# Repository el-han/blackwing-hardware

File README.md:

# Blackwing keyboard

The Blackwing keyboard is a vertically staggered split keyboard inspired by the [Mitosis keyboard](https://github.com/reversebias/mitosis).

## Features

- QMK firmware
- Cherry MX switches
- nRF52840 module
- NKRO as each switch is wired to its own GPIO
- Nordic's proprietary low power radio protocol
- Uses the receiver from the [Mitosis keyboard](https://github.com/reversebias/mitosis)
- Runs months to years on battery as it stays in deep sleep until a button is pressed or released
- PCB plate for plate mounted switches

## Todo

- Merge firmware into QMK project
- Use nRF 52840 dongle as receiver
- Build a ZMK based firmware
- Add Bluetooth support

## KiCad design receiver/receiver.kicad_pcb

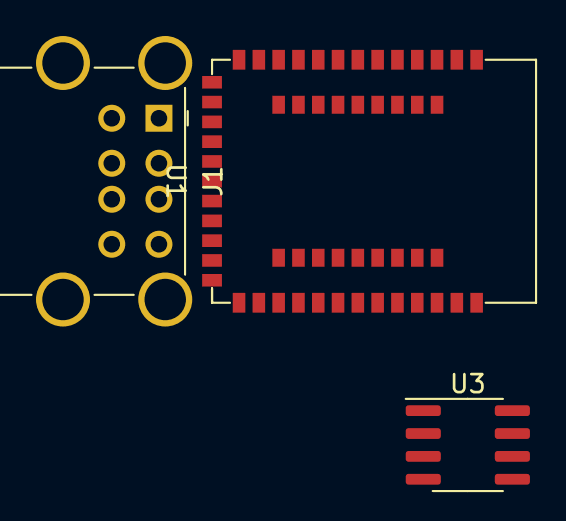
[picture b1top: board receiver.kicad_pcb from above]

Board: 2 copper layers, 4 parts (1 on the bottom side), 4 nets, no tracks yet.

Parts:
J1: USB_A; USB_A_Wuerth_61400826021_Horizontal_Stacked
U1: HOLYIOT-18010-NRF52840
U2: ATmega32U4-A; TQFP-44_10x10mm_P0.8mm
U3: AMS1117CS-3.3; SOIC-8_3.9x4.9mm_P1.27mm

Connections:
unnamed: U2.14 (VCC), U2.34 (VCC)
unnamed: U2.15 (GND), U2.23 (GND), U2.35 (GND), U2.43 (GND)
unnamed: U2.24 (AVCC), U2.44 (AVCC)
unnamed: U3.2 (VO), U3.3 (VO), U3.6 (VO), U3.7 (VO)

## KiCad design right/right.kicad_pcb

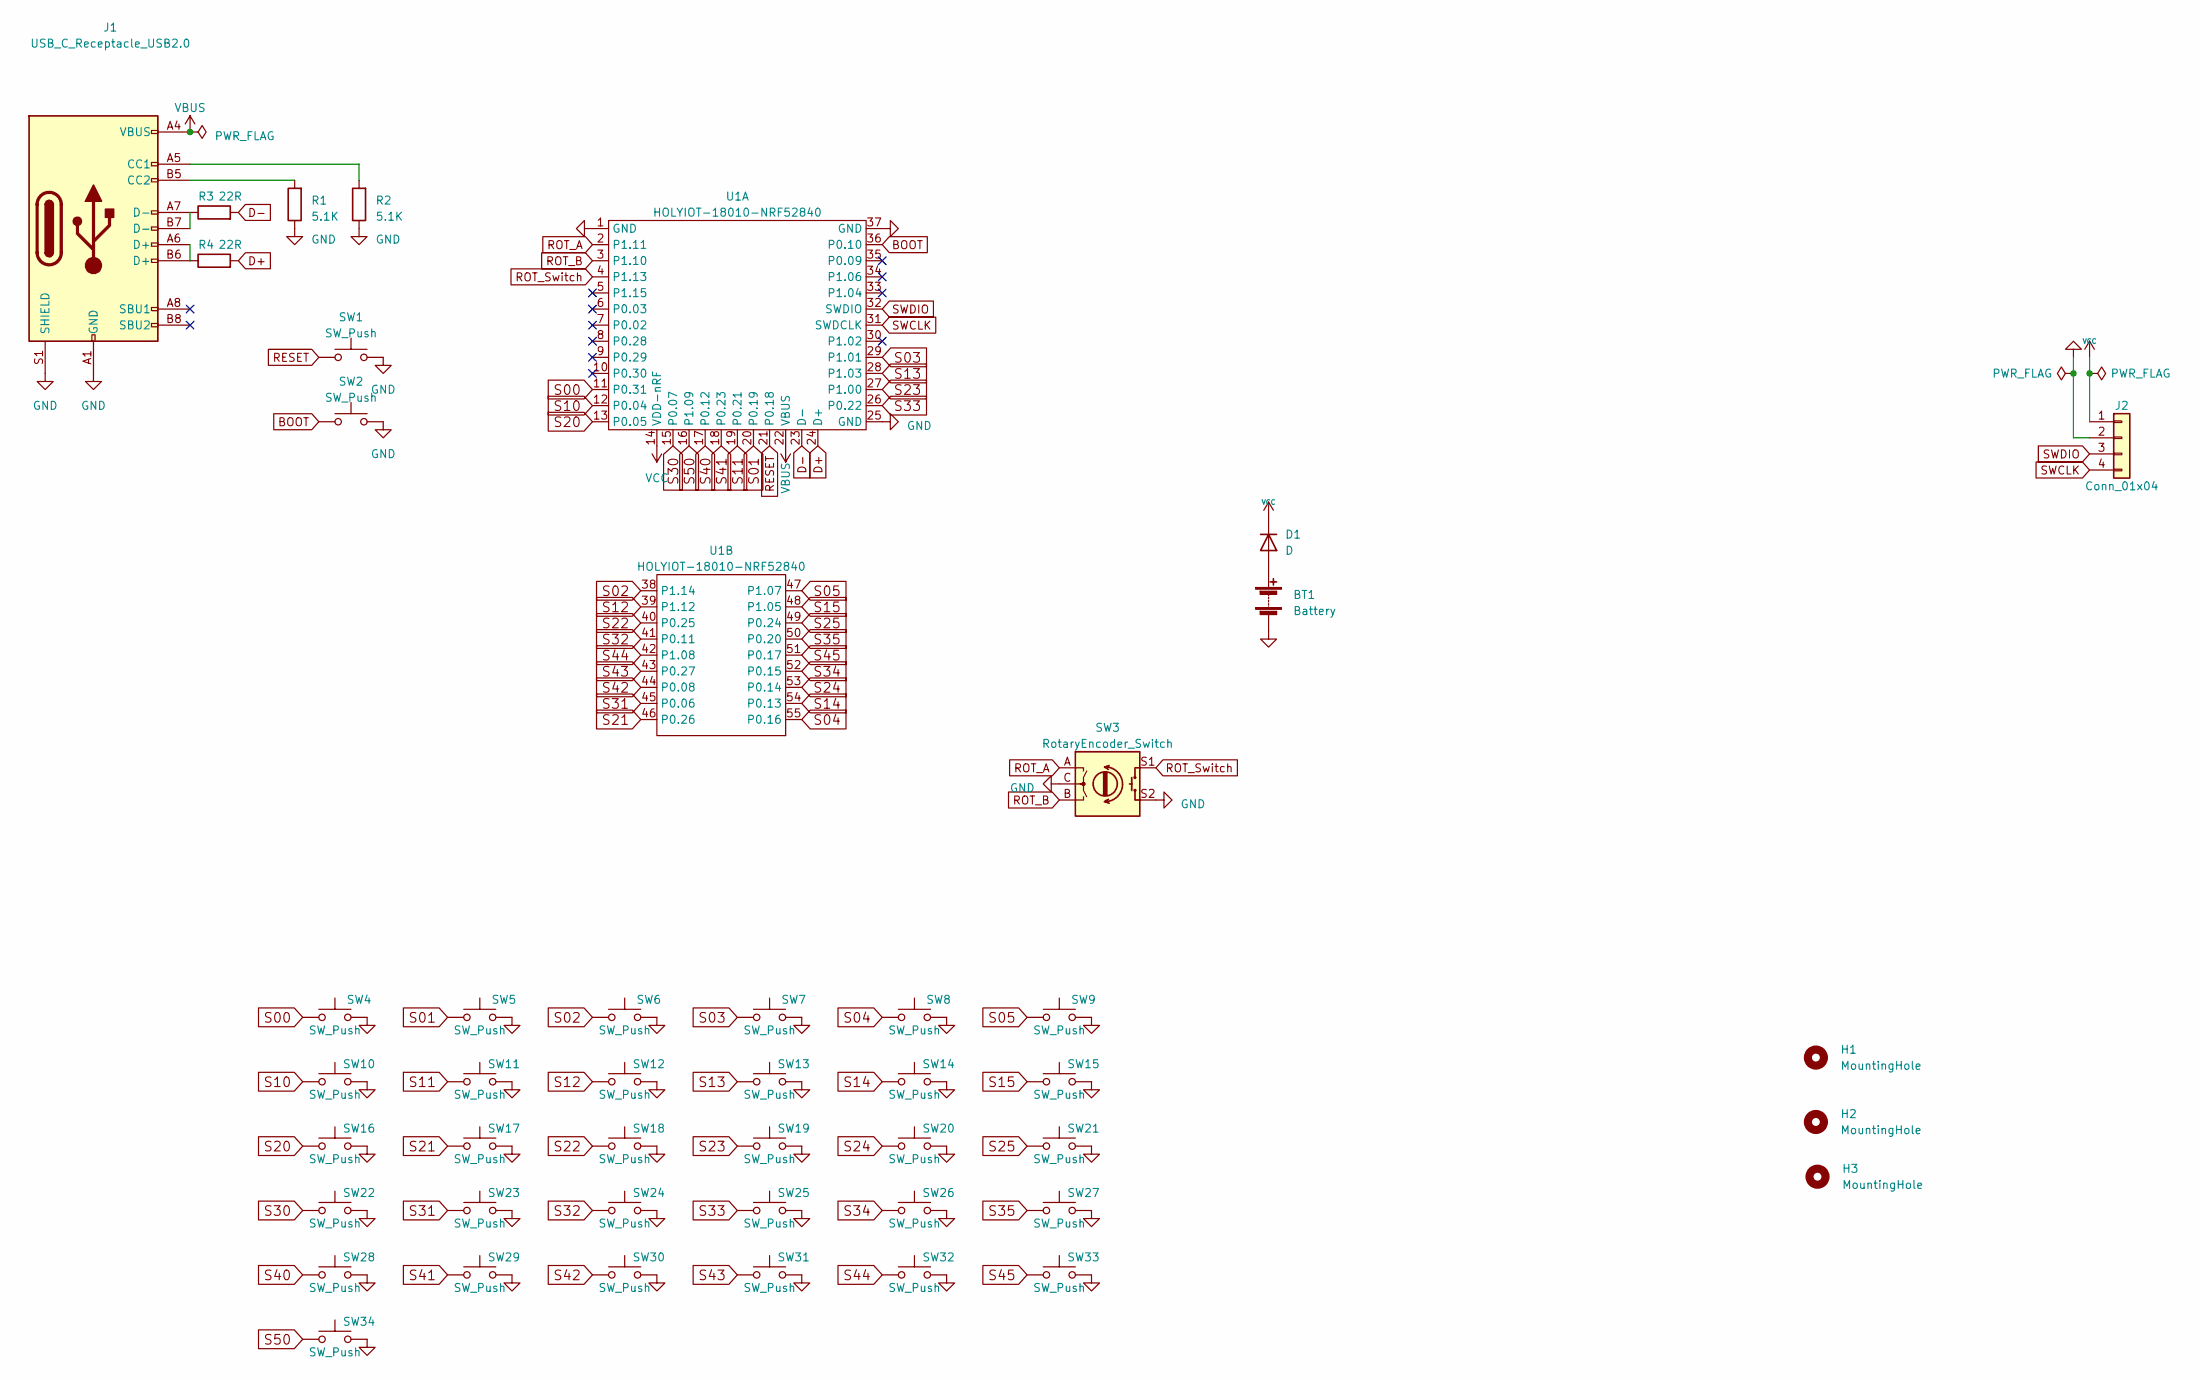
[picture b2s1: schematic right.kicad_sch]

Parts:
BT1: Battery; BatteryHolder_Keystone_2468_2xAAA
D1: D; D_SOD-123
H1, H2, H3: MountingHole; MountingHole_2.7mm_M2.5_DIN965
J1: USB_C_Receptacle_USB2.0; USB_C_Receptacle_GCT_USB4085
J2: Conn_01x04; Programming_Header
R1, R2: 5.1K; R_0603_1608Metric
R3, R4: 22R; R_0402_1005Metric
SW1, SW2: SW_Push; SW_Push_1P1T_NO_Vertical_Wuerth_434133025816
SW3: RotaryEncoder_Switch; RotaryEncoder_Alps_EC12E-Switch_Vertical_H20mm
SW4, SW5, SW6, SW7, SW8, SW9, SW10, SW11, SW12, SW13, SW14, SW15, SW16, SW17, SW18, SW19, SW20, SW21, SW22, SW23, SW24, SW25, SW26, SW27, SW28, SW29, SW30, SW32: SW_Push; SW_Cherry_MX_1.00u_PCB
SW31, SW33: SW_Push; SW_Cherry_MX_1.25u_PCB
SW34: SW_Push; SW_Cherry_MX_1.75u_PCB
U1: HOLYIOT-18010-NRF52840

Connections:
BOOT: SW2.1, U1.36 (P0.10)
D+: R4.2, U1.24 (D+)
D-: R3.2, U1.23 (D-)
GND: BT1.2 (-), J1.A1 (GND), J1.A12 (GND), J1.B1 (GND), J1.B12 (GND), J1.S1 (SHIELD), J2.2, R1.1, R2.1, SW1.2, SW2.2, SW3.C, SW3.S2, SW4.2, SW5.2, SW6.2, SW7.2, SW8.2, SW9.2, SW10.2, SW11.2, SW12.2, SW13.2, SW14.2, SW15.2, SW16.2, SW17.2, SW18.2, SW19.2, SW20.2, SW21.2, SW22.2, SW23.2, SW24.2, SW25.2, SW26.2, SW27.2, SW28.2, SW29.2, SW30.2, SW31.2, SW32.2, SW33.2, SW34.2, U1.1 (GND), U1.25 (GND), U1.37 (GND)
unnamed: BT1.1 (+), D1.2 (A)
unnamed: J1.A5 (CC1), R2.2
unnamed: J1.A6 (D+), J1.B6 (D+), R4.1
unnamed: J1.A7 (D-), J1.B7 (D-), R3.1
unnamed: J1.B5 (CC2), R1.2
RESET: SW1.1, U1.21 (P0.18)
ROT_A: SW3.A, U1.2 (P1.11)
ROT_B: SW3.B, U1.3 (P1.10)
ROT_Switch: SW3.S1, U1.4 (P1.13)
S00: SW4.1, U1.11 (P0.31)
S01: SW5.1, U1.20 (P0.19)
S02: SW6.1, U1.38 (P1.14)
S03: SW7.1, U1.29 (P1.01)
S04: SW8.1, U1.55 (P0.16)
S05: SW9.1, U1.47 (P1.07)
S10: SW10.1, U1.12 (P0.04)
S11: SW11.1, U1.19 (P0.21)
S12: SW12.1, U1.39 (P1.12)
S13: SW13.1, U1.28 (P1.03)
S14: SW14.1, U1.54 (P0.13)
S15: SW15.1, U1.48 (P1.05)
S20: SW16.1, U1.13 (P0.05)
S21: SW17.1, U1.46 (P0.26)
S22: SW18.1, U1.40 (P0.25)
S23: SW19.1, U1.27 (P1.00)
S24: SW20.1, U1.53 (P0.14)
S25: SW21.1, U1.49 (P0.24)
S30: SW22.1, U1.15 (P0.07)
S31: SW23.1, U1.45 (P0.06)
S32: SW24.1, U1.41 (P0.11)
S33: SW25.1, U1.26 (P0.22)
S34: SW26.1, U1.52 (P0.15)
S35: SW27.1, U1.50 (P0.20)
S40: SW28.1, U1.17 (P0.12)
S41: SW29.1, U1.18 (P0.23)
S42: SW30.1, U1.44 (P0.08)
S43: SW31.1, U1.43 (P0.27)
S44: SW32.1, U1.42 (P1.08)
S45: SW33.1, U1.51 (P0.17)
S50: SW34.1, U1.16 (P1.09)
SWCLK: J2.4, U1.31 (SWDCLK)
SWDIO: J2.3, U1.32 (SWDIO)
VBUS: J1.A4 (VBUS), J1.A9 (VBUS), J1.B4 (VBUS), J1.B9 (VBUS), U1.22 (VBUS)
VCC: D1.1 (K), J2.1, U1.14 (VDD-nRF)

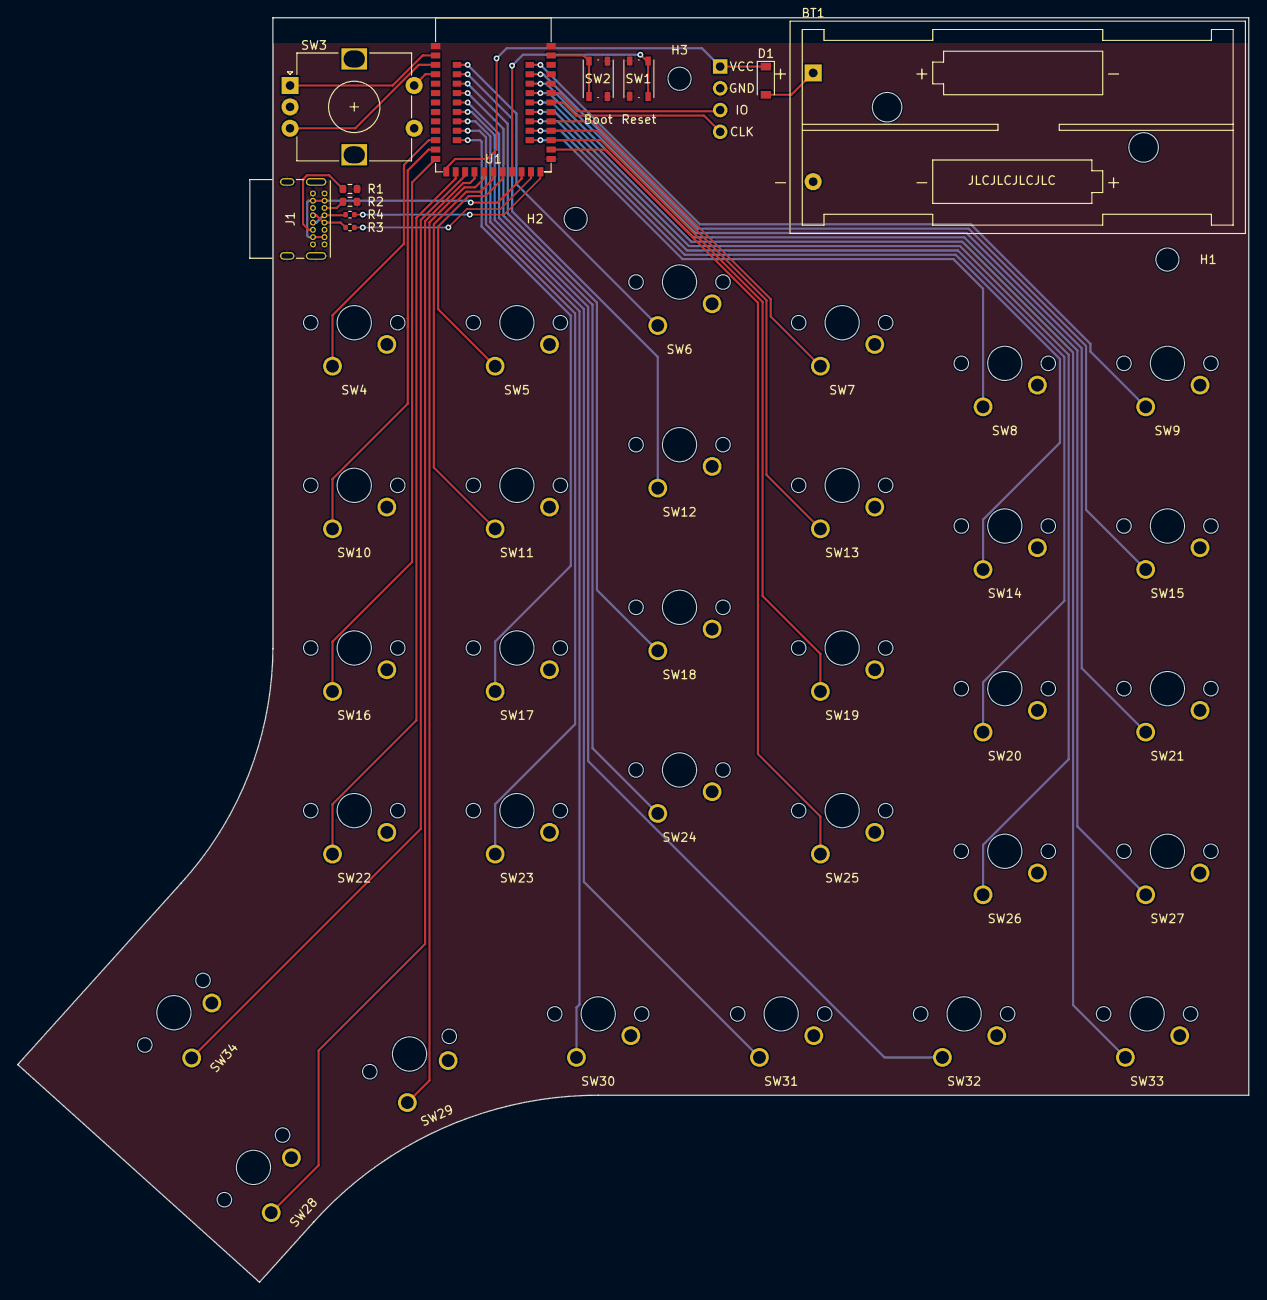
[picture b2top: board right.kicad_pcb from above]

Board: 2 copper layers, 143.8 x 147.7 mm, 46 parts (0 on the bottom side), 48 nets.

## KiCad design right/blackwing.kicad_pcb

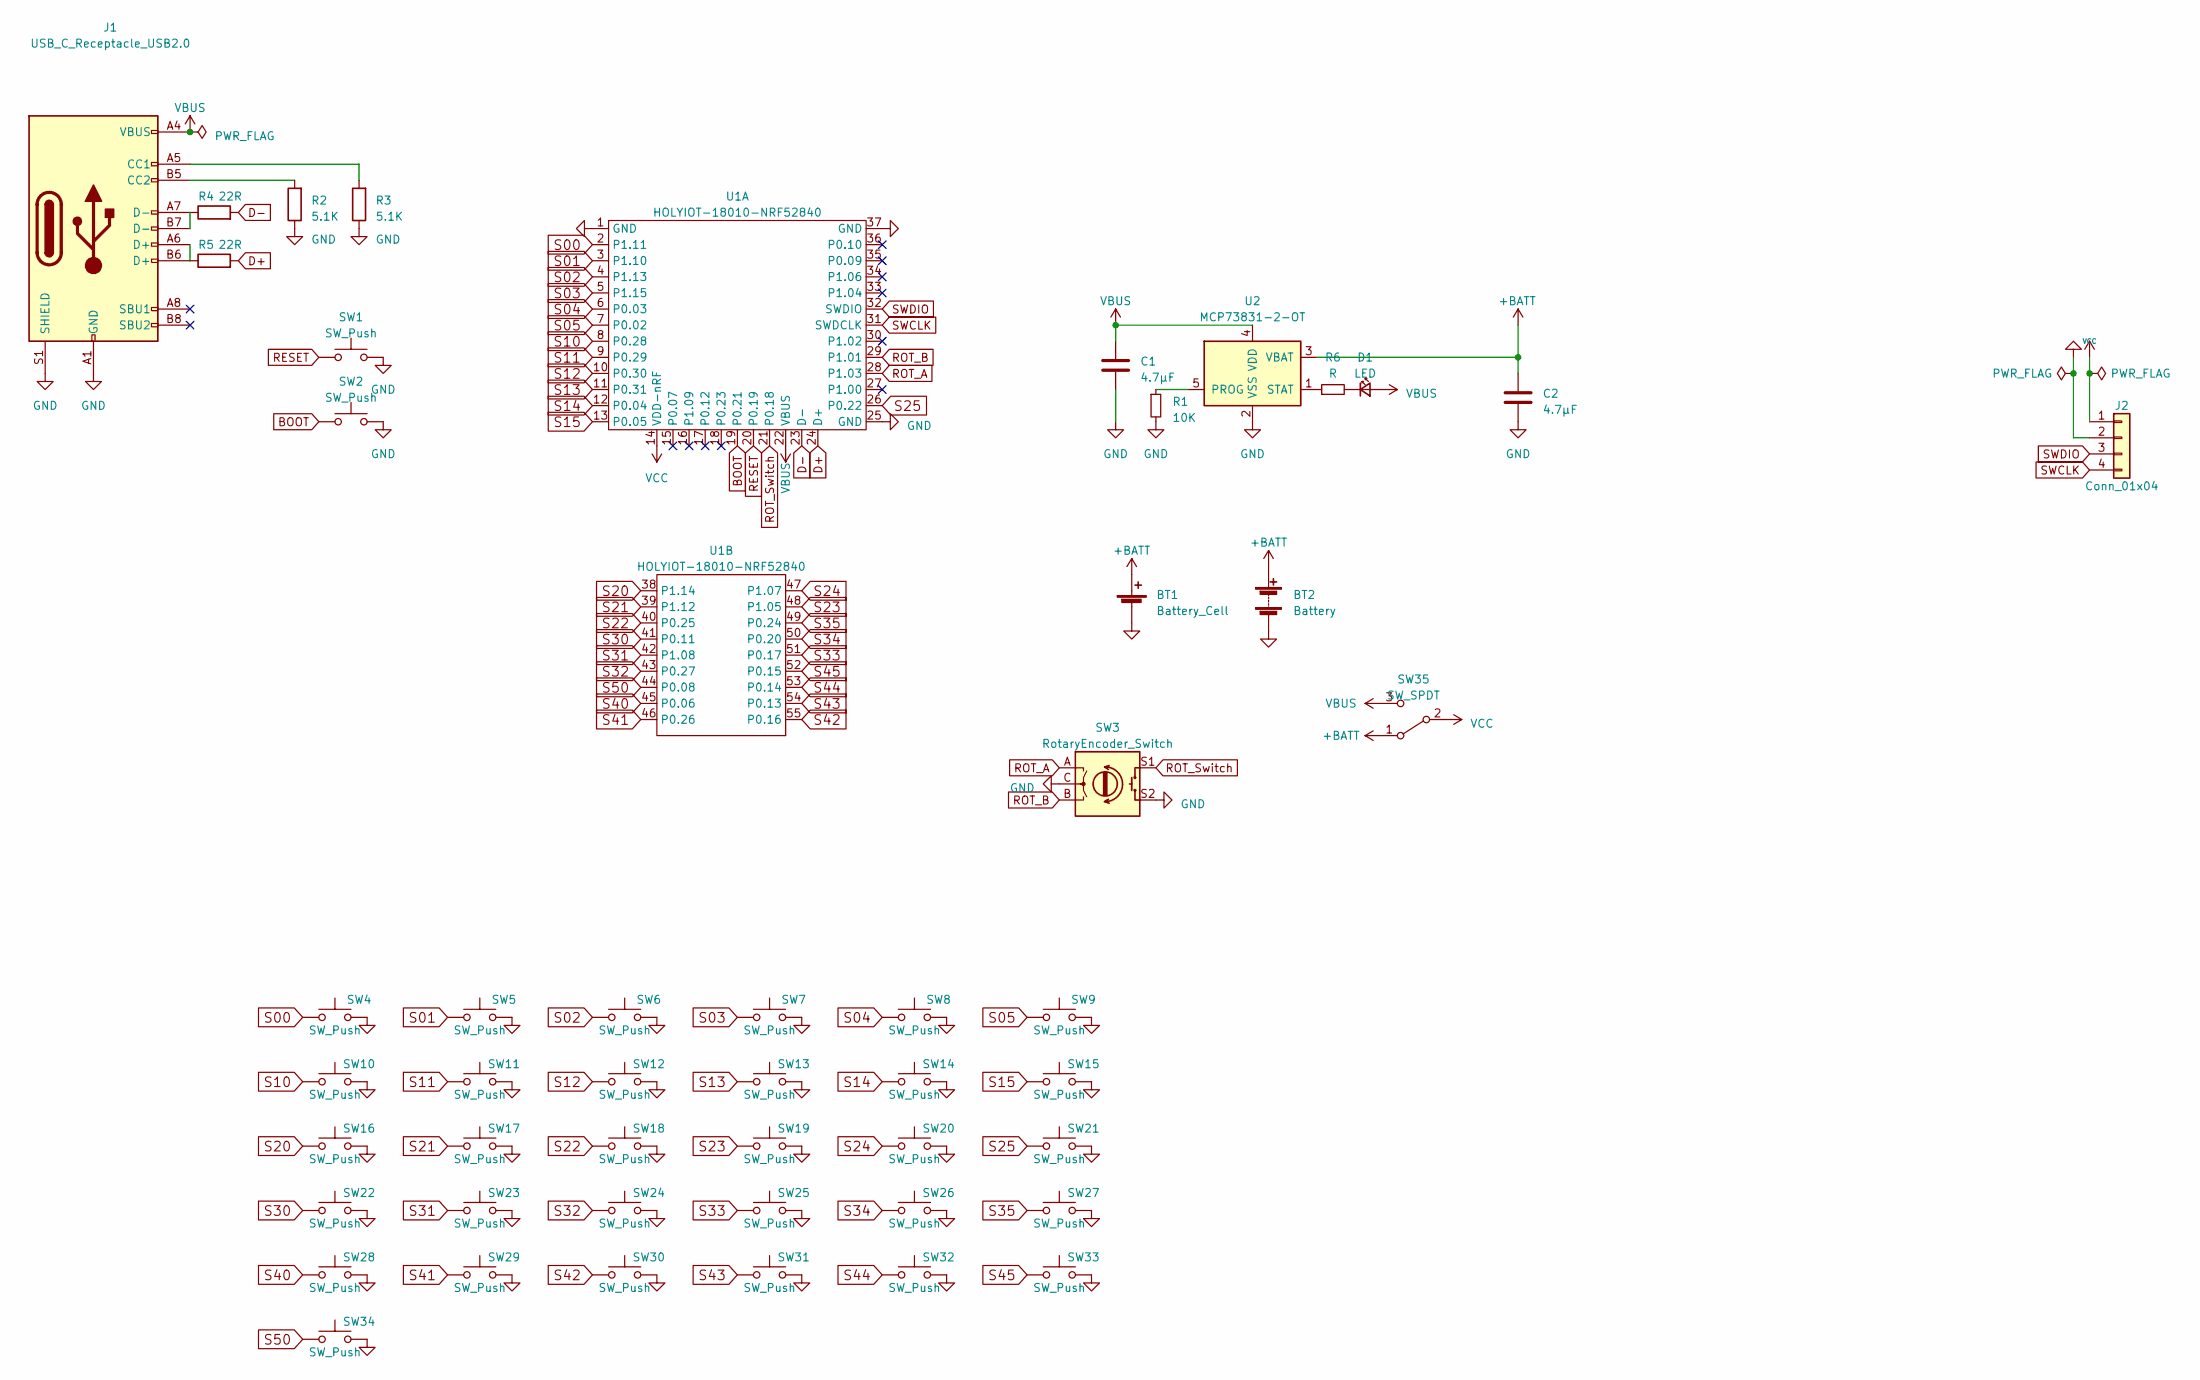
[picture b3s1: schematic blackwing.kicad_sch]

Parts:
BT1: Battery_Cell; JST_PH_S2B-PH-K_1x02_P2.00mm_Horizontal
BT2: Battery; BatteryHolder_Keystone_2468_2xAAA
C1, C2: 4.7µF; C_0603_1608Metric
D1: LED; LED_0603_1608Metric
J1: USB_C_Receptacle_USB2.0; USB_C_Receptacle_GCT_USB4085
J2: Conn_01x04; Programming_Header
R1: 10K; R_0603_1608Metric
R2, R3: 5.1K; R_0603_1608Metric
R4, R5: 22R; R_0402_1005Metric
R6: R; R_0603_1608Metric
SW1, SW2: SW_Push; SW_Push_1P1T_NO_Vertical_Wuerth_434133025816
SW3: RotaryEncoder_Switch; RotaryEncoder_Alps_EC12E-Switch_Vertical_H20mm
SW4, SW5, SW6, SW7, SW8, SW9, SW10, SW11, SW12, SW13, SW14, SW15, SW16, SW17, SW18, SW19, SW20, SW21, SW22, SW23, SW24, SW25, SW26, SW27, SW28, SW29, SW30, SW32: SW_Push; SW_Cherry_MX_1.00u_PCB
SW31, SW33: SW_Push; SW_Cherry_MX_1.25u_PCB
SW34: SW_Push; SW_Cherry_MX_1.50u_PCB
SW35: SW_SPDT; SW_CuK_OS102011MA1QN1_SPDT_Angled
U1: HOLYIOT-18010-NRF52840
U2: MCP73831-2-OT; SOT-23-5

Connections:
+BATT: BT1.1 (+), BT2.1 (+), C2.1, SW35.1 (A), U2.3 (VBAT)
BOOT: SW2.1, U1.19 (P0.21)
D+: R5.2, U1.24 (D+)
D-: R4.2, U1.23 (D-)
GND: BT1.2 (-), BT2.2 (-), C1.2, C2.2, J1.A1 (GND), J1.A12 (GND), J1.B1 (GND), J1.B12 (GND), J1.S1 (SHIELD), J2.2, R1.2, R2.1, R3.1, SW1.2, SW2.2, SW3.C, SW3.S2, SW4.2, SW5.2, SW6.2, SW7.2, SW8.2, SW9.2, SW10.2, SW11.2, SW12.2, SW13.2, SW14.2, SW15.2, SW16.2, SW17.2, SW18.2, SW19.2, SW20.2, SW21.2, SW22.2, SW23.2, SW24.2, SW25.2, SW26.2, SW27.2, SW28.2, SW29.2, SW30.2, SW31.2, SW32.2, SW33.2, SW34.2, U1.1 (GND), U1.25 (GND), U1.37 (GND), U2.2 (VSS)
unnamed: D1.1 (K), R6.2
unnamed: J1.A5 (CC1), R3.2
unnamed: J1.A6 (D+), J1.B6 (D+), R5.1
unnamed: J1.A7 (D-), J1.B7 (D-), R4.1
unnamed: J1.B5 (CC2), R2.2
unnamed: R1.1, U2.5 (PROG)
unnamed: R6.1, U2.1 (STAT)
RESET: SW1.1, U1.20 (P0.19)
ROT_A: SW3.A, U1.28 (P1.03)
ROT_B: SW3.B, U1.29 (P1.01)
ROT_Switch: SW3.S1, U1.21 (P0.18)
S00: SW4.1, U1.2 (P1.11)
S01: SW5.1, U1.3 (P1.10)
S02: SW6.1, U1.4 (P1.13)
S03: SW7.1, U1.5 (P1.15)
S04: SW8.1, U1.6 (P0.03)
S05: SW9.1, U1.7 (P0.02)
S10: SW10.1, U1.8 (P0.28)
S11: SW11.1, U1.9 (P0.29)
S12: SW12.1, U1.10 (P0.30)
S13: SW13.1, U1.11 (P0.31)
S14: SW14.1, U1.12 (P0.04)
S15: SW15.1, U1.13 (P0.05)
S20: SW16.1, U1.38 (P1.14)
S21: SW17.1, U1.39 (P1.12)
S22: SW18.1, U1.40 (P0.25)
S23: SW19.1, U1.48 (P1.05)
S24: SW20.1, U1.47 (P1.07)
S25: SW21.1, U1.26 (P0.22)
S30: SW22.1, U1.41 (P0.11)
S31: SW23.1, U1.42 (P1.08)
S32: SW24.1, U1.43 (P0.27)
S33: SW25.1, U1.51 (P0.17)
S34: SW26.1, U1.50 (P0.20)
S35: SW27.1, U1.49 (P0.24)
S40: SW28.1, U1.45 (P0.06)
S41: SW29.1, U1.46 (P0.26)
S42: SW30.1, U1.55 (P0.16)
S43: SW31.1, U1.54 (P0.13)
S44: SW32.1, U1.53 (P0.14)
S45: SW33.1, U1.52 (P0.15)
S50: SW34.1, U1.44 (P0.08)
SWCLK: J2.4, U1.31 (SWDCLK)
SWDIO: J2.3, U1.32 (SWDIO)
VBUS: C1.1, D1.2 (A), J1.A4 (VBUS), J1.A9 (VBUS), J1.B4 (VBUS), J1.B9 (VBUS), SW35.3 (C), U1.22 (VBUS), U2.4 (VDD)
VCC: J2.1, SW35.2 (B), U1.14 (VDD-nRF)

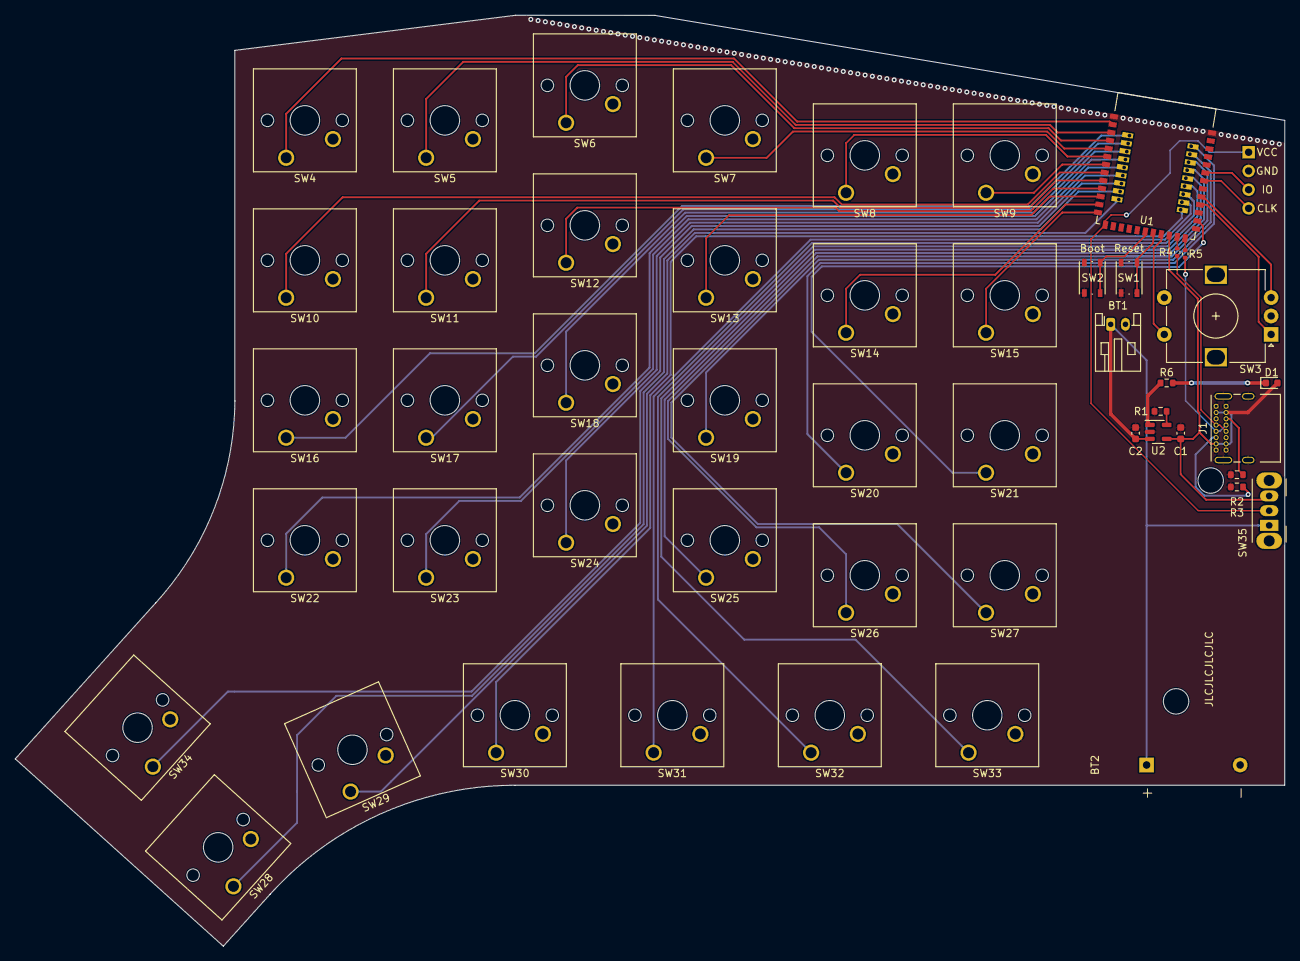
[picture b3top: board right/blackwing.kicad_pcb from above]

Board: 2 copper layers, 172.3 x 126.4 mm, 50 parts (0 on the bottom side), 51 nets.

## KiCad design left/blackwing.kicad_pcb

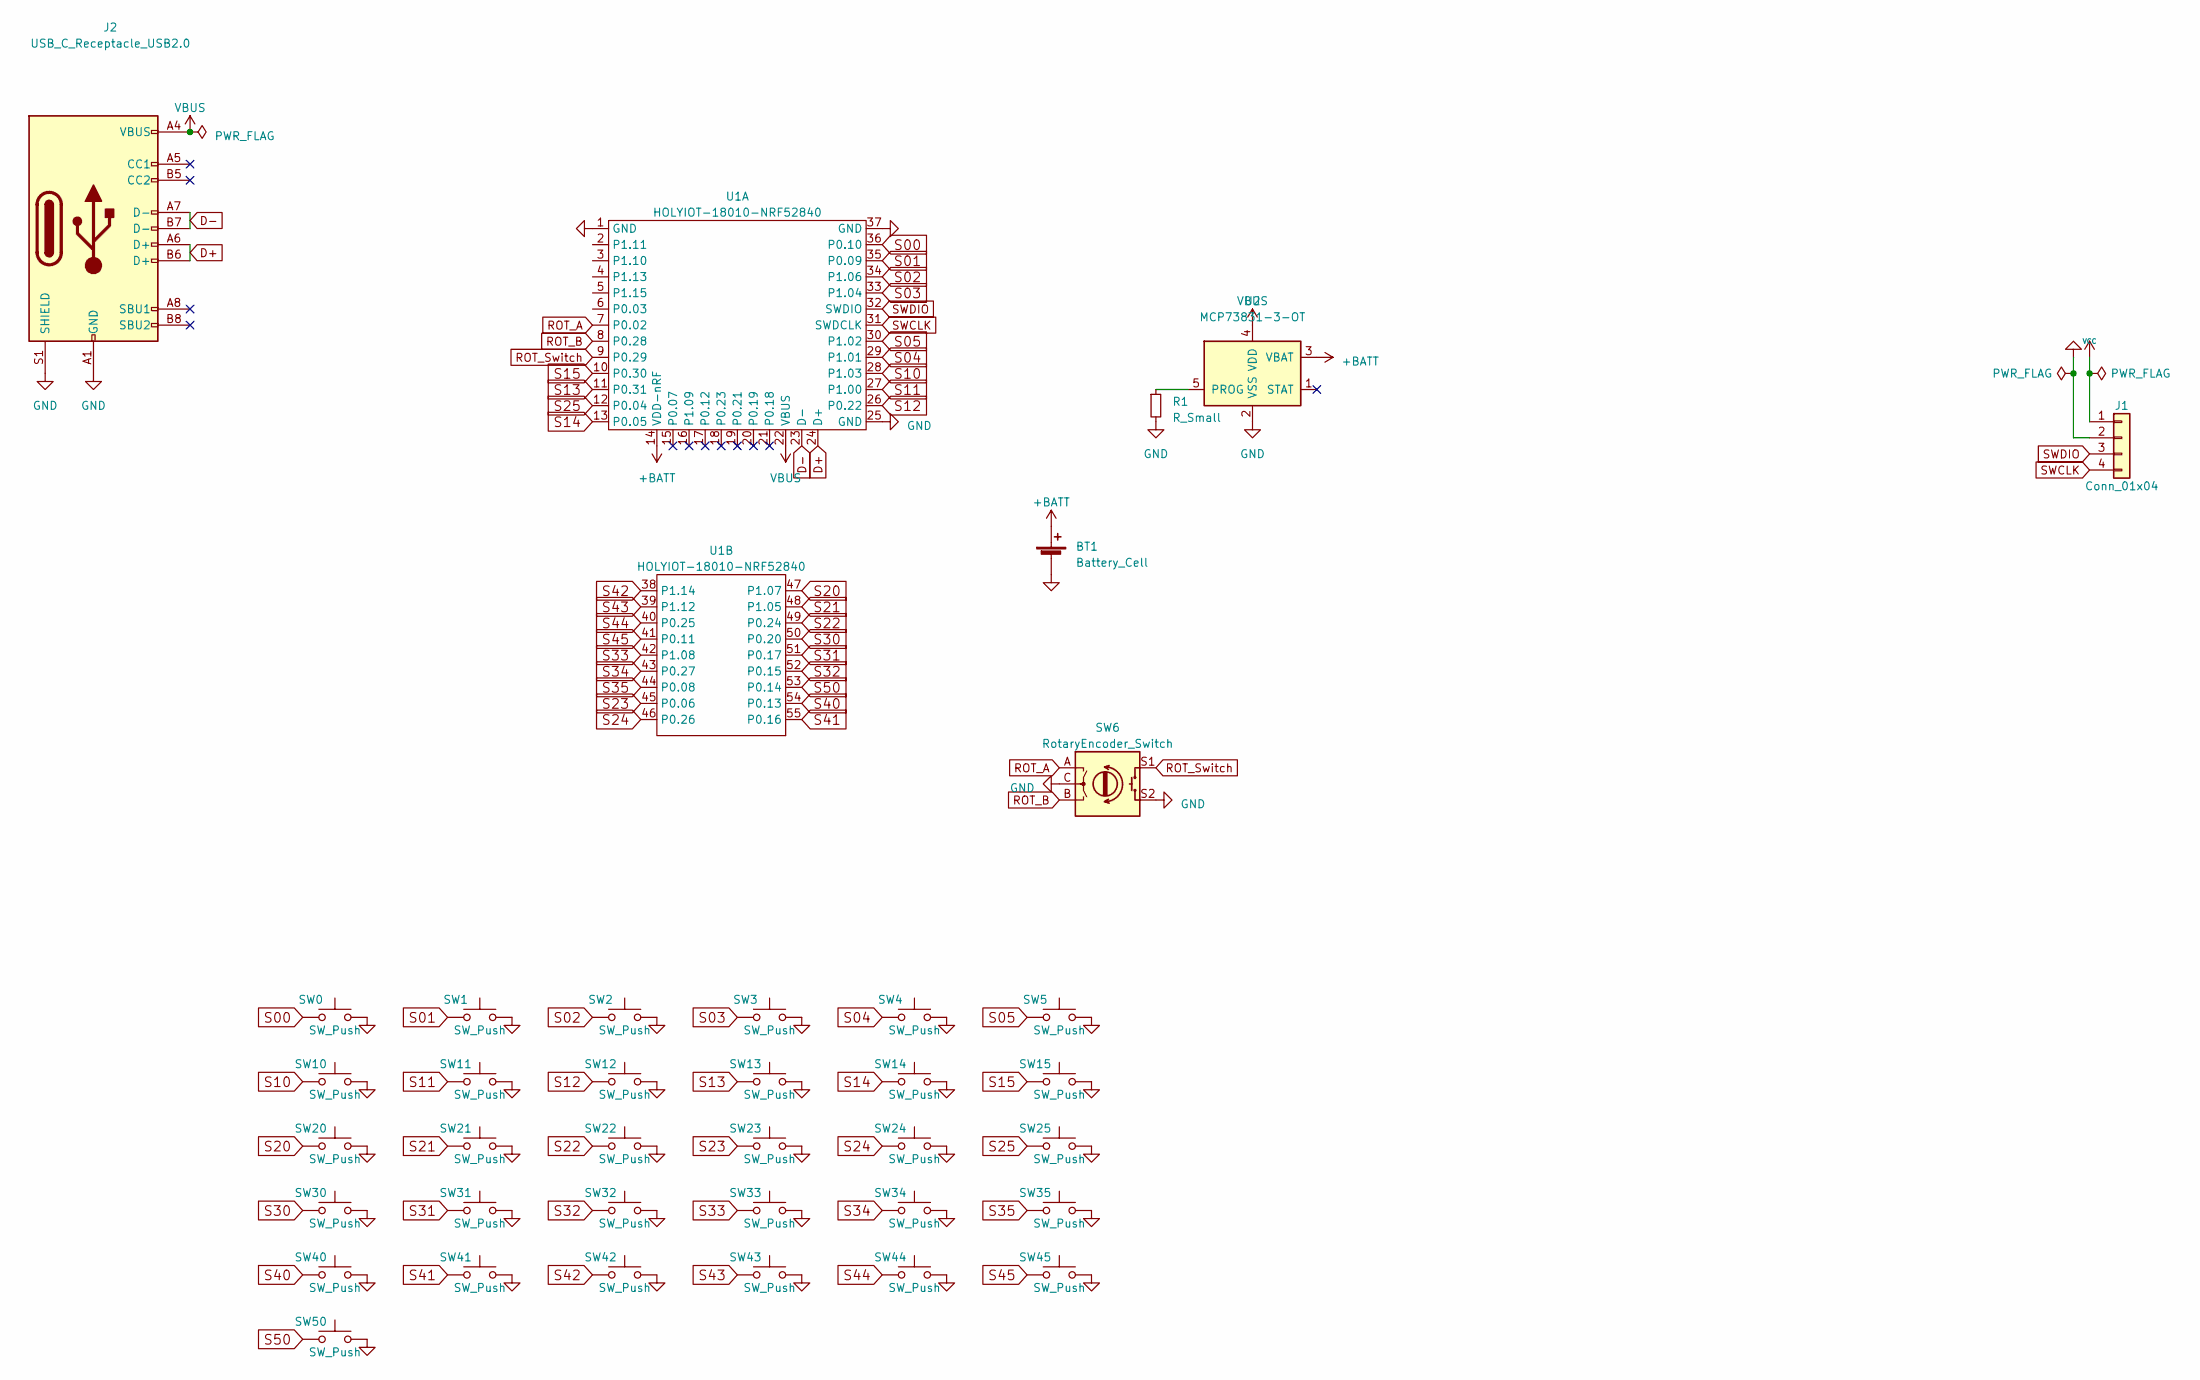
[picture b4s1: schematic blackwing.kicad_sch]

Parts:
BT1: Battery_Cell; JST_PH_S2B-PH-K_1x02_P2.00mm_Horizontal
J1: Conn_01x04; Programming_Header
J2: USB_C_Receptacle_USB2.0; USB_C_Receptacle_GCT_USB4085
R1: R_Small; R_0603_1608Metric
SW0, SW1, SW2, SW3, SW4, SW5, SW10, SW11, SW12, SW13, SW14, SW15, SW20, SW21, SW22, SW23, SW24, SW25, SW30, SW31, SW32, SW33, SW34, SW35, SW40, SW41, SW42, SW44, SW50: SW_Push; MX_FLIP_5Pin
SW6: RotaryEncoder_Switch; RotaryEncoder_Alps_EC12E-Switch_Vertical_H20mm
SW43, SW45: SW_Push; MX_FLIP_5Pin_1.25u
U1: HOLYIOT-18010-NRF52840
U2: MCP73831-3-OT; SOT-23-5

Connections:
+BATT: BT1.1 (+), U1.14 (VDD-nRF), U2.3 (VBAT)
D+: J2.A6 (D+), J2.B6 (D+), U1.24 (D+)
D-: J2.A7 (D-), J2.B7 (D-), U1.23 (D-)
GND: BT1.2 (-), J1.2, J2.A1 (GND), J2.A12 (GND), J2.B1 (GND), J2.B12 (GND), J2.S1 (SHIELD), R1.2, SW0.1, SW1.1, SW2.1, SW3.1, SW4.1, SW5.1, SW6.C, SW6.S2, SW10.1, SW11.1, SW12.1, SW13.1, SW14.1, SW15.1, SW20.1, SW21.1, SW22.1, SW23.1, SW24.1, SW25.1, SW30.1, SW31.1, SW32.1, SW33.1, SW34.1, SW35.1, SW40.1, SW41.1, SW42.1, SW43.1, SW44.1, SW45.1, SW50.1, U1.1 (GND), U1.25 (GND), U1.37 (GND), U2.2 (VSS)
unnamed: R1.1, U2.5 (PROG)
ROT_A: SW6.A, U1.7 (P0.02)
ROT_B: SW6.B, U1.8 (P0.28)
ROT_Switch: SW6.S1, U1.9 (P0.29)
S00: SW0.2, U1.36 (P0.10)
S01: SW1.2, U1.35 (P0.09)
S02: SW2.2, U1.34 (P1.06)
S03: SW3.2, U1.33 (P1.04)
S04: SW4.2, U1.29 (P1.01)
S05: SW5.2, U1.30 (P1.02)
S10: SW10.2, U1.28 (P1.03)
S11: SW11.2, U1.27 (P1.00)
S12: SW12.2, U1.26 (P0.22)
S13: SW13.2, U1.11 (P0.31)
S14: SW14.2, U1.13 (P0.05)
S15: SW15.2, U1.10 (P0.30)
S20: SW20.2, U1.47 (P1.07)
S21: SW21.2, U1.48 (P1.05)
S22: SW22.2, U1.49 (P0.24)
S23: SW23.2, U1.45 (P0.06)
S24: SW24.2, U1.46 (P0.26)
S25: SW25.2, U1.12 (P0.04)
S30: SW30.2, U1.50 (P0.20)
S31: SW31.2, U1.51 (P0.17)
S32: SW32.2, U1.52 (P0.15)
S33: SW33.2, U1.42 (P1.08)
S34: SW34.2, U1.43 (P0.27)
S35: SW35.2, U1.44 (P0.08)
S40: SW40.2, U1.54 (P0.13)
S41: SW41.2, U1.55 (P0.16)
S42: SW42.2, U1.38 (P1.14)
S43: SW43.2, U1.39 (P1.12)
S44: SW44.2, U1.40 (P0.25)
S45: SW45.2, U1.41 (P0.11)
S50: SW50.2, U1.53 (P0.14)
SWCLK: J1.4, U1.31 (SWDCLK)
SWDIO: J1.3, U1.32 (SWDIO)
VBUS: J2.A4 (VBUS), J2.A9 (VBUS), J2.B4 (VBUS), J2.B9 (VBUS), U1.22 (VBUS), U2.4 (VDD)
VCC: J1.1

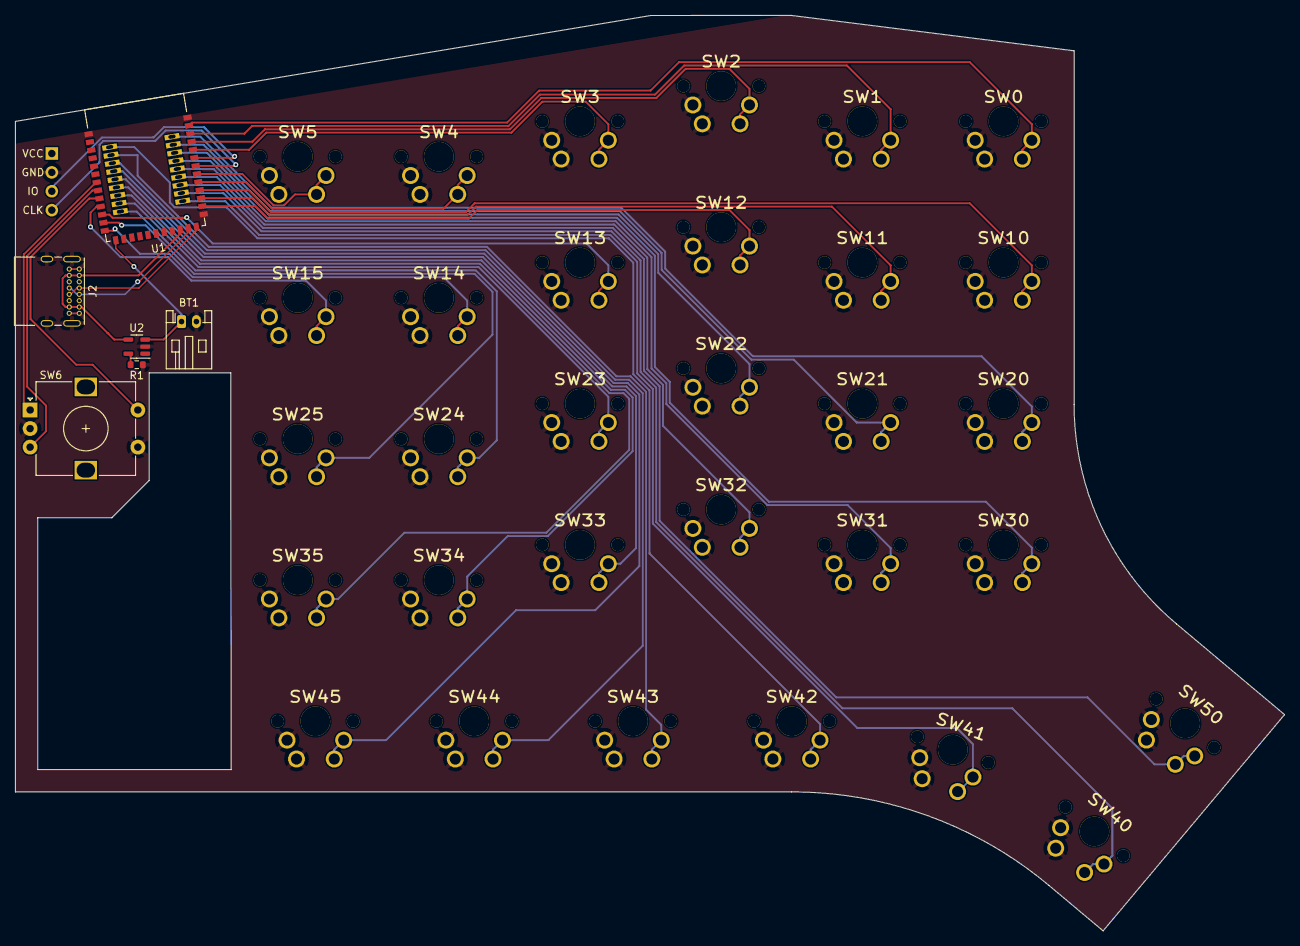
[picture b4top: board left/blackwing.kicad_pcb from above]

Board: 2 copper layers, 170.8 x 123.2 mm, 38 parts (1 on the bottom side), 42 nets.

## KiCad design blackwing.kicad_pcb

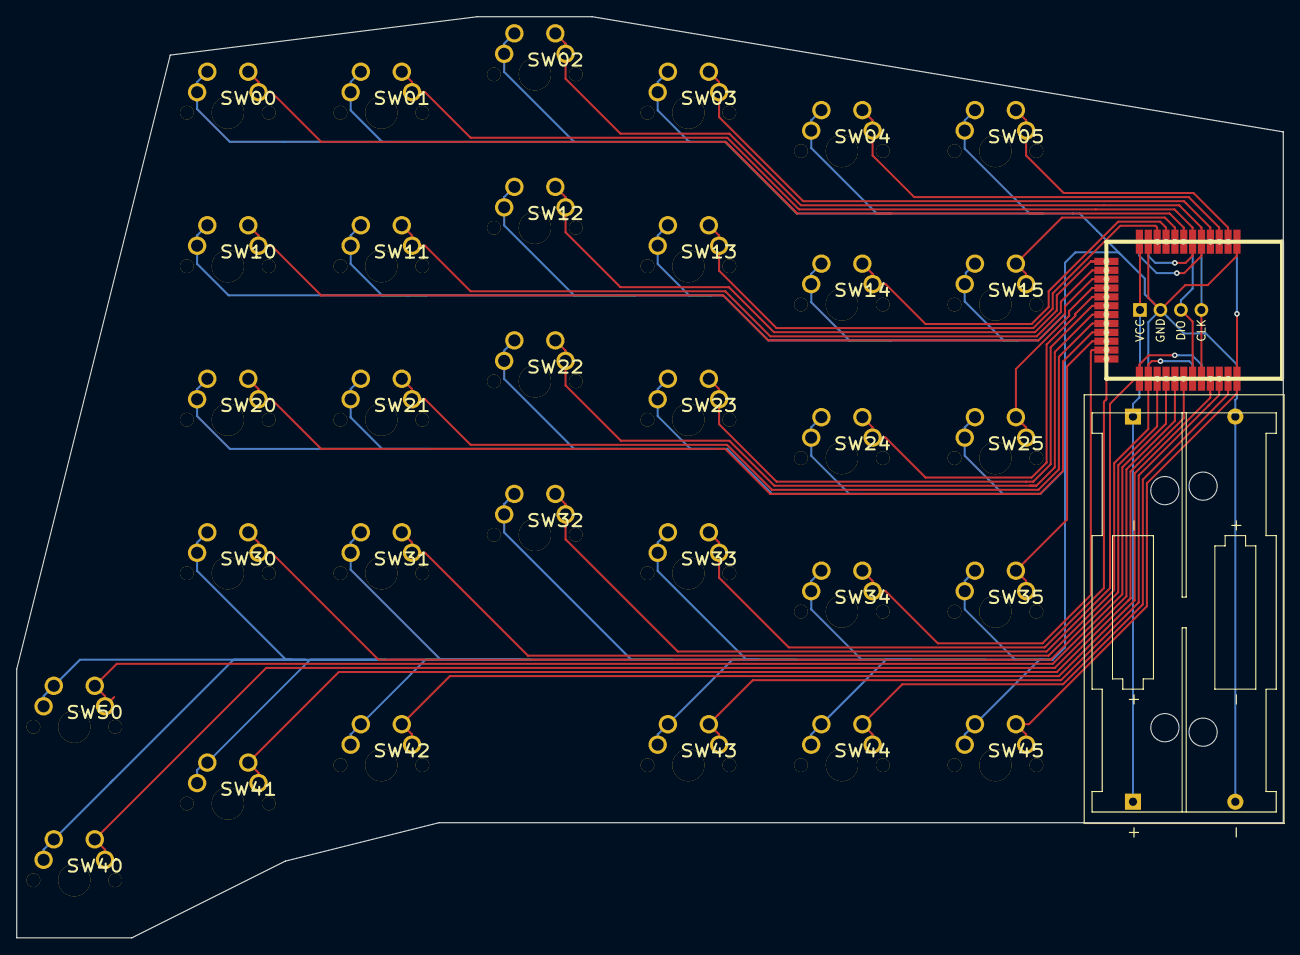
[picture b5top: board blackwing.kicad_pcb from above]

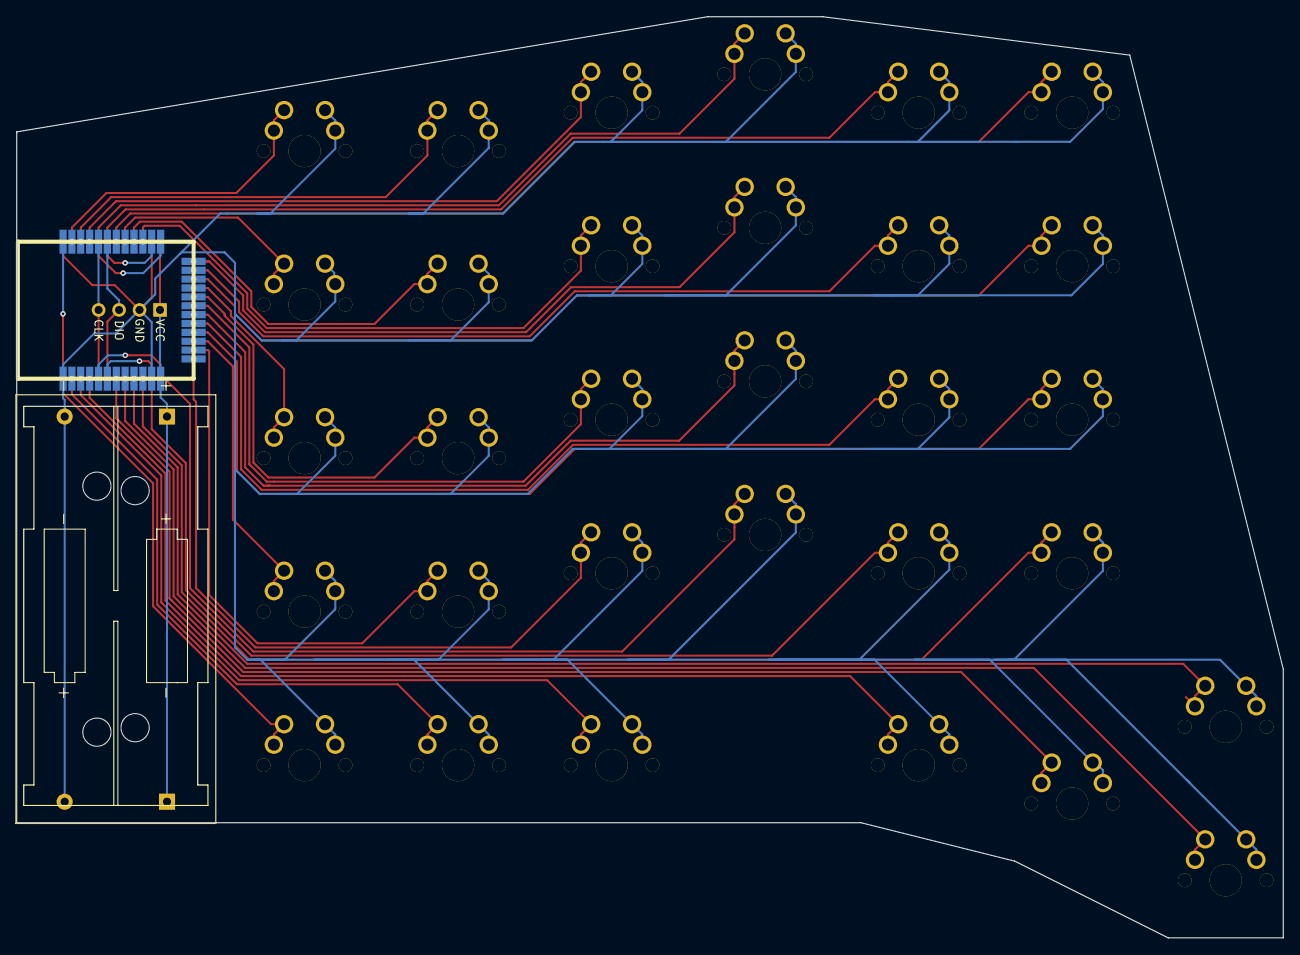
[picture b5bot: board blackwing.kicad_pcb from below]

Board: 2 copper layers, 157.2 x 114.3 mm, 36 parts (3 on the bottom side), 35 nets.

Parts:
BT1, BT2: Battery; Keystone_2468_2xAAA
J1: Conn_01x04; Programming_Header
SW00, SW01, SW02, SW03, SW04, SW05, SW10, SW11, SW12, SW13, SW14, SW15, SW20, SW21, SW22, SW23, SW24, SW25, SW30, SW31, SW32, SW33, SW34, SW35, SW40, SW41, SW42, SW43, SW44, SW45, SW50: SW_Push; MX_FLIP
U1, U2: CORE51822; Core51822

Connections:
GND: BT1.2, BT2.2, J1.2, SW00.2, SW01.2, SW02.2, SW03.2, SW04.2, SW05.2, SW10.2, SW11.2, SW12.2, SW13.2, SW14.2, SW15.2, SW20.2, SW21.2, SW22.2, SW23.2, SW24.2, SW25.2, SW30.2, SW31.2, SW32.2, SW33.2, SW34.2, SW35.2, SW40.2, SW41.2, SW42.2, SW43.2, SW44.2, SW45.2, SW50.2, U1.1, U1.11, U2.1, U2.11
unnamed: J1.3, U1.31, U2.31
unnamed: J1.4, U1.32, U2.32
S00: SW00.1, U1.30, U2.7
S01: SW01.1, U1.26, U2.6
S02: SW02.1, U1.25, U2.5
S03: SW03.1, U1.33, U2.4
S04: SW04.1, U1.34, U2.3
S05: SW05.1, U1.35, U2.2
S10: SW10.1, U1.22, U2.15
S11: SW11.1, U1.23, U2.14
S12: SW12.1, U1.24, U2.13
S13: SW13.1, U1.27, U2.10
S14: SW14.1, U1.28, U2.9
S15: SW15.1, U1.29, U2.8
S20: SW20.1, U1.16, U2.21
S21: SW21.1, U1.17, U2.20
S22: SW22.1, U1.18, U2.19
S23: SW23.1, U1.19, U2.18
S24: SW24.1, U1.20, U2.17
S25: SW25.1, U1.21, U2.16
S30: SW30.1, U1.10, U2.27
S31: SW31.1, U1.6, U2.26
S32: SW32.1, U1.5, U2.25
S33: SW33.1, U1.13, U2.24
S34: SW34.1, U1.14, U2.23
S35: SW35.1, U1.15, U2.22
S40: SW40.1, U1.8, U2.29
S41: SW41.1, U1.7, U2.30
S42: SW42.1, U1.4, U2.33
S43: SW43.1, U1.3, U2.34
S44: SW44.1, U1.2, U2.35
S45: SW45.1, U1.36, U2.36
S50: SW50.1, U1.9, U2.28
VCC: BT1.1, BT2.1, J1.1, U1.12, U2.12

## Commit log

2018-05-02 vertically staggered design
2018-08-08 convert to kicad 5.0
2018-09-17 version 2
2018-09-17 v 2.1
2018-09-18 make outline smaller
2018-10-06 move key columns
2021-07-15 redesign, batteries on the outer edge
2021-07-17 right finished, left wip
2021-07-18 finish left
2021-07-18 move footprint library to commen directory
2021-07-18 clean up
2021-07-18 clean up further
2021-07-18 add all system footprint libraries
2021-07-20 update footprint of rf module
2021-07-20 minor fixes
2021-08-09 add datasheet for radio module
2022-07-29 add receiver and update file versions
2024-10-25 add readme
2026-05-19 Add license file
